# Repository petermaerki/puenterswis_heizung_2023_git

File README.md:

# puenterswis_heizung_2023
Puenterswis Heizungsersatz mit jeweils zwei Pellematic Maxi in Kaskade, PESK41, mit Brennwert, Touch V.4.04.
Steuerung der Ladung der dezentralen Wärmespeicher und des zentralen Pufferspeichers.

- [Erfahrungsbericht](./erfahrung_doku/readme.md)

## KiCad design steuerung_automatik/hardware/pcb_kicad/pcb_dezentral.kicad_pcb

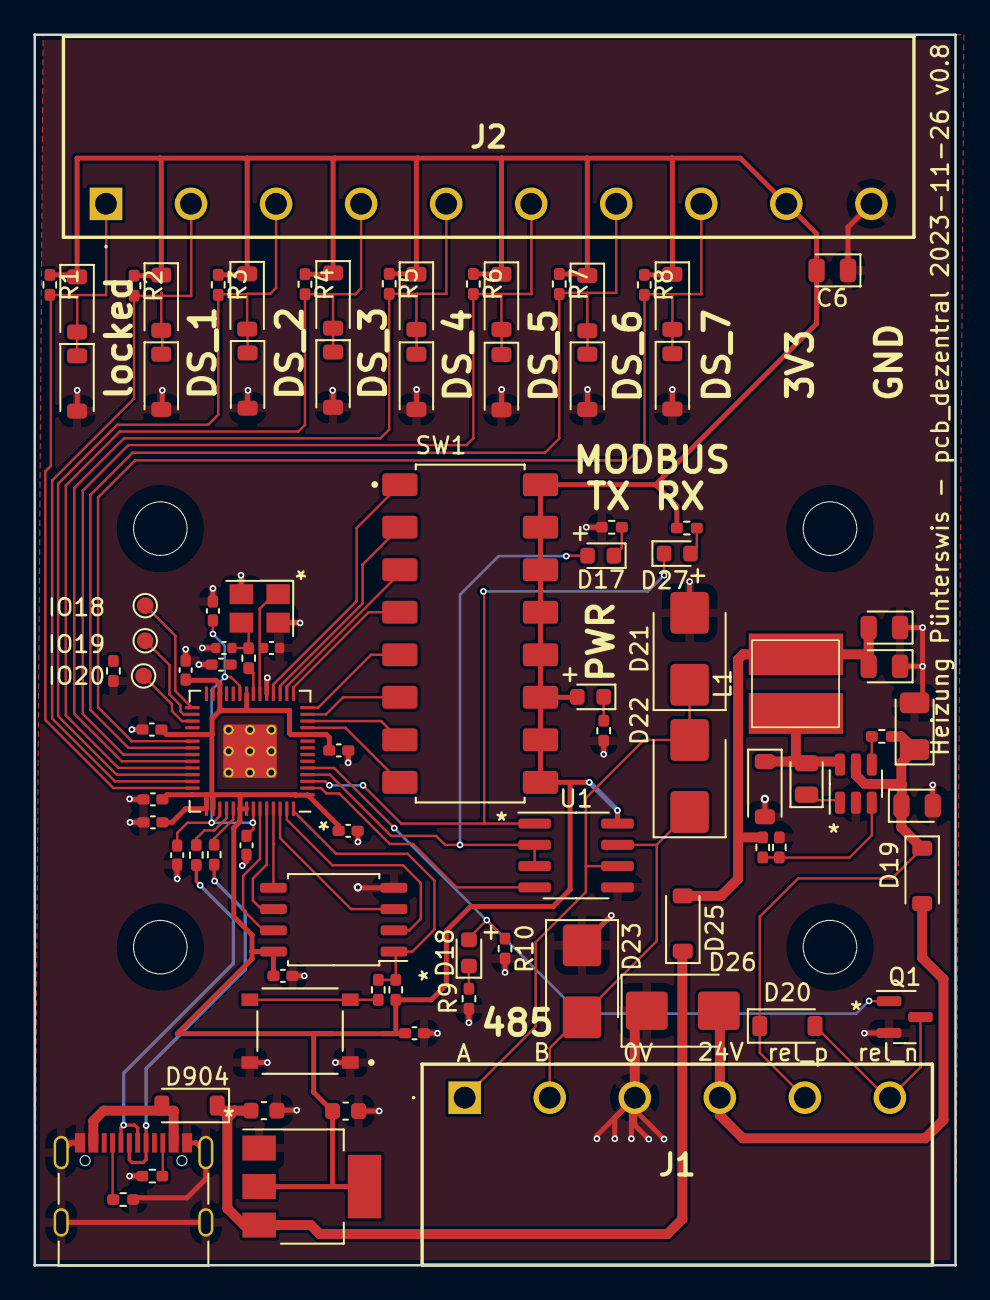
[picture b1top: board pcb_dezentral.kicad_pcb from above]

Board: 2 copper layers, 55.0 x 73.5 mm, 92 parts (0 on the bottom side), 58 nets.

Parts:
C1: 4u7 50V; D_1206_3216Metric
C2, C3, C5, C6: 100n 50V; D_0805_2012Metric
C4: 10u 25V; D_0805_2012Metric
C901, C902: 10u; C_0603_1608Metric
C903, C904, C907, C908, C911, C912, C913, C914, C915, C916: 100n; C_0402_1005Metric_Pad0.74x0.62mm_HandSolder
C905, C906: 1u; C_0402_1005Metric_Pad0.74x0.62mm_HandSolder
C909, C910: 30p; C_0402_1005Metric
D1, D2, D3, D4, D5, D6, D7, D8, D9, D10, D11, D12, D13, D14, D15, D16, D19, D20, D24, D25, D904: B5819W SL; D_SOD-123
D17: LED RED; LED_0603_1608Metric
D18: LED WHITE; LED_0603_1608Metric
D21, D22, D23: SMBJ6.5CA; D_SMB
D26: SMBJ30CA; D_SMB
D27: LED BLUE; LED_0603_1608Metric
D901: LED GREEN; LED_0603_1608Metric
HOLDER1: din_rail_pcb_holder
IO18, IO19, IO20: TestPoint; TestPoint_Pad_D1.0mm
J1: weidmueller_SL5.08HC-06-90
J2: weidmueller_SL5.08HC-10-90
J901: USB_C_Receptacle_USB2.0; USB_C_Receptacle_Palconn_UTC16-G
L1: 22uH; L_MODBUS
Q1: AO3400A; SOT-23
R1, R2, R3, R4, R5, R6, R7, R8, R14: 4k7; R_0402_1005Metric_Pad0.72x0.64mm_HandSolder
R9: 470; R_0402_1005Metric_Pad0.72x0.64mm_HandSolder
R10, R13: 10k; R_0402_1005Metric_Pad0.72x0.64mm_HandSolder
R11: 100k; R_0402_1005Metric_Pad0.72x0.64mm_HandSolder
R12: 56k; R_0402_1005Metric_Pad0.72x0.64mm_HandSolder
R15, R16, R905: 470R; R_0402_1005Metric_Pad0.72x0.64mm_HandSolder
R901, R902: 5.1K; R_0402_1005Metric_Pad0.72x0.64mm_HandSolder
R903, R904: 27R; R_0402_1005Metric_Pad0.72x0.64mm_HandSolder
R906: 1K; R_0402_1005Metric_Pad0.72x0.64mm_HandSolder
R907: 10K; R_0402_1005Metric_Pad0.72x0.64mm_HandSolder
R908: 1k; R_0402_1005Metric_Pad0.72x0.64mm_HandSolder
SW1: dip_switch_SPST16
SW901: SW_MEC_5E; SW_TS-1187A-B-A-B
U1: SP3485EN-L/TR; SOIC-8_3.9x4.9mm_P1.27mm
U2: AOZ1282CI; SOT-23-6
U901: RP2040; RP2040-QFN-56
U902: AMS1117-3.3; SOT-223-3_TabPin2
U903: W25Q128JVS; SOIC-8_5.23x5.23mm_P1.27mm
Y901: Crystal_GND24_Small; Crystal_SMD_3225-4Pin_3.2x2.5mm

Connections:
24Vp: C1.1, C2.1, D19.1 (K), D20.1 (K), J1.5, R11.1, U2.5 (VIN)
485_24V: D19.2 (A), D26.2 (A2), J1.4
485_A: D21.1 (A1), D22.2 (A2), J1.1, U1.6 (A)
485_B: D22.1 (A1), D23.2 (A2), J1.2, U1.7 (B)
+1V1: C903.1, C904.1, C905.1, U901.23 (DVDD), U901.45 (VREG-VOUT), U901.50 (DVDD)
+3V3: C6.2, C902.1, C906.1, C907.1, C908.1, C911.1, C912.1, C913.1, C914.1, C915.1, C916.1, D1.1 (K), D3.1 (K), D5.1 (K), D7.1 (K), D9.1 (K), D11.1 (K), D13.1 (K), D15.1 (K), D901.2 (A), J2.9, R1.1, R2.1, R3.1, R4.1, R5.1, R6.1, R7.1, R8.1, R15.1, R907.1, SW1.1-1, SW1.2-1, SW1.3-1, SW1.4-1, SW1.5-1, SW1.6-1, SW1.7-1, SW1.8-1, U1.8 (VCC), U901.1 (IOVDD), U901.10 (IOVDD), U901.22 (IOVDD), U901.26 (RUN), U901.33 (IOVDD), U901.42 (IOVDD), U901.43 (ADC-AVDD), U901.44 (VREG-VIN), U901.48 (USB-VDD), U901.49 (IOVDD), U902.2 (VO), U903.8 (VCC)
+5V: C901.1, D25.1 (K), D904.1 (K), U902.3 (VI)
/cpu/QSPI_SCLK: U901.52 (QSPI-SCLK), U903.6 (CLK)
/cpu/QSPI_SD0: U901.53 (QSPI-SD0), U903.5 (DI(IO0))
/cpu/QSPI_SD1: U901.55 (QSPI-SD1), U903.2 (DO(IO1))
/cpu/QSPI_SD2: U901.54 (QSPI-SD2), U903.3 (IO2)
/cpu/QSPI_SD3: U901.51 (QSPI-SD3), U903.7 (IO3)
/cpu/QSPI_SS: R906.2, R907.2, U901.56 (QSPI-SS-N), U903.1 (~CS)
/cpu/USB_D+: J901.A6 (D+), J901.B6 (D+), R903.1
/cpu/USB_D-: J901.A7 (D-), J901.B7 (D-), R904.1
/cpu/XIN: C909.1, U901.20 (XIN), Y901.1
/cpu/XOUT: R908.1, U901.21 (XOUT)
GND: C1.2, C2.2, C4.1, C5.1, C6.1, C901.2, C902.2, C903.2, C904.2, C905.2, C906.2, C907.2, C908.2, C909.2, C910.2, C911.2, C912.2, C913.2, C914.2, C915.2, C916.2, D2.2 (A), D4.2 (A), D6.2 (A), D8.2 (A), D10.2 (A), D12.2 (A), D14.2 (A), D16.2 (A), D21.2 (A2), D23.1 (A1), D24.2 (A), D26.1 (A1), J1.3, J2.10, J901.A1 (GND), J901.A12 (GND), J901.B1 (GND), J901.B12 (GND), J901.S1 (SHIELD), Q1.2 (S), R9.2, R10.2, R13.2, R14.2, R16.2, R901.2, R902.2, R905.1, SW901.1, SW901.2, U1.5 (GND), U2.2 (GND), U901.19 (TESTEN), U901.57 (GND), U902.1 (GND), U903.4 (GND), Y901.2, Y901.4
MODBUS_DE: D17.2 (A), R14.1, U1.2 (~RE), U1.3 (DE), U901.4 (GPIO2)
MODBUS_DI: U1.4 (DI), U901.2 (GPIO0)
MODBUS_RO: D27.1 (K), U1.1 (RO), U901.3 (GPIO1)
unnamed: C910.1, R908.2, Y901.3
unnamed: D17.1 (K), R16.1
unnamed: D18.1 (K), R9.1
unnamed: C3.2, D24.1 (K), L1.1, U2.6 (LX)
unnamed: C4.2, C5.2, D25.2 (A), L1.2, R12.2
unnamed: D27.2 (A), R15.2
unnamed: D901.1 (K), R905.2
unnamed: D904.2 (A), J901.A4 (VBUS), J901.A9 (VBUS), J901.B4 (VBUS), J901.B9 (VBUS)
unnamed: J901.A5 (CC1), R901.1
unnamed: J901.B5 (CC2), R902.1
unnamed: R906.1, SW901.3 (K), SW901.4 (A)
unnamed: C3.1, U2.1 (BST)
unnamed: R11.2, U2.4 (EN)
unnamed: R12.1, R13.1, U2.3 (FB)
unnamed: IO18.1, U901.29 (GPIO18)
unnamed: IO19.1, U901.30 (GPIO19)
unnamed: IO20.1, U901.31 (GPIO20)
unnamed: R904.2, U901.46 (USB-DM)
unnamed: R903.2, U901.47 (USB-DP)
ds_0: D1.2 (A), D2.1 (K), J2.1, R1.2, U901.41 (GPIO29/ADC3)
ds_1: D3.2 (A), D4.1 (K), J2.2, R2.2, U901.40 (GPIO28/ADC2)
ds_2: D5.2 (A), D6.1 (K), J2.3, R3.2, U901.39 (GPIO27/ADC1)
ds_3: D7.2 (A), D8.1 (K), J2.4, R4.2, U901.38 (GPIO26/ADC0)
ds_4: D9.2 (A), D10.1 (K), J2.5, R5.2, U901.37 (GPIO25)
ds_5: D11.2 (A), D12.1 (K), J2.6, R6.2, U901.36 (GPIO24)
ds_6: D13.2 (A), D14.1 (K), J2.7, R7.2, U901.35 (GPIO23)
ds_7: D15.2 (A), D16.1 (K), J2.8, R8.2, U901.34 (GPIO22)
modbus_addr_0: SW1.1, U901.18 (GPIO15)
modbus_addr_1: SW1.2, U901.17 (GPIO14)
modbus_addr_2: SW1.3, U901.16 (GPIO13)
modbus_addr_3: SW1.4, U901.15 (GPIO12)
modbus_addr_4: SW1.5, U901.14 (GPIO11)
modbus_addr_5: SW1.6, U901.13 (GPIO10)
modbus_addr_6: SW1.7, U901.12 (GPIO9)
modbus_addr_7: SW1.8, U901.11 (GPIO8)
rel: D18.2 (A), Q1.1 (G), R10.1, U901.5 (GPIO3)
rel_n: D20.2 (A), J1.6, Q1.3 (D)

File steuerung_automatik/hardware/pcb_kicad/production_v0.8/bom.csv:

Designator,Footprint,Quantity,Value,LCSC Part #
C1,1206,1,4u7 50V,C515689
"C2, C3, C5, C6",0805,4,100n 50V,C49678
C4,0805,1,10u 25V,C15850
"C901, C902",0603,2,10u,
"C903, C904, C907, C908, C911, C912, C913, C914, C915, C916",0402,10,100n,
"C905, C906",0402,2,1u,
"C909, C910",0402,2,30p,C1570
"D1, D10, D11, D12, D13, D14, D15, D16, D19, D2, D20, D24, D25, D3, D4, D5, D6, D7, D8, D9, D904",D_SOD-123,21,B5819W SL,C8598
D17,0603,1,LED RED,C2286
D18,0603,1,LED WHITE,C2290
"D21, D22, D23",D_SMB,3,SMBJ6.5CA,C7420377
D26,D_SMB,1,SMBJ30CA,C353367
D27,0603,1,LED BLUE,C189307
D901,0603,1,LED GREEN,C2297
J901,USB_C_Receptacle_Palconn_UTC16-G,1,USB_C_Receptacle_USB2.0,C165948
L1,L_MODBUS,1,22uH,C5289423
Q1,SOT-23,1,AO3400A,C20917
"R1, R14, R2, R3, R4, R5, R6, R7, R8",0402,9,4k7,
"R10, R13, R907",0402,3,10k,
R11,0402,1,100k,
R12,0402,1,56k,
"R15, R16, R905",0402,3,470R,
R9,0402,1,470,
"R901, R902",0402,2,5.1K,
"R903, R904",0402,2,27R,
"R906, R908",0402,2,1K,
SW1,dip_switch_SPST16,1,dip_switch_SPST16,C470473
SW901,SW_TS-1187A-B-A-B,1,SW_MEC_5E,C318884
U1,SOIC-8_3.9x4.9mm_P1.27mm,1,SP3485EN-L/TR,C8963
U2,SOT-23-6,1,AOZ1282CI,C111916
U901,RP2040-QFN-56,1,RP2040,C2040
U902,SOT-223-3_TabPin2,1,AMS1117-3.3,C6186
U903,SOIC-8_5.23x5.23mm_P1.27mm,1,W25Q128JVS,C97521
Y901,Crystal_SMD_3225-4Pin_3.2x2.5mm,1,Crystal_GND24_Small,C9002

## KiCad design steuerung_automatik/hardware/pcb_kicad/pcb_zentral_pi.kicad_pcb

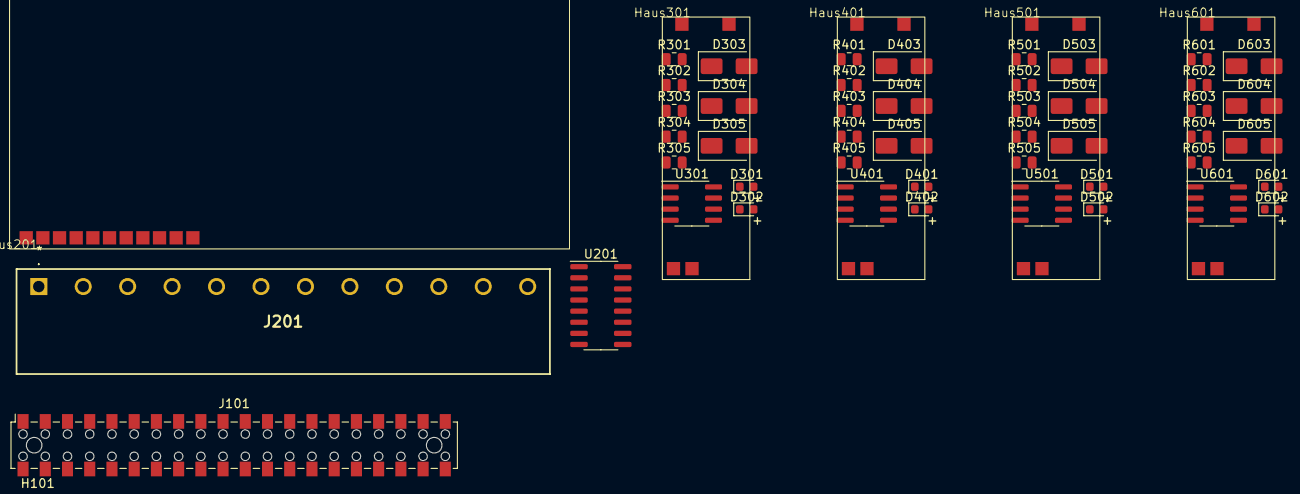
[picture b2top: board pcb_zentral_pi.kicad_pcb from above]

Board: 2 copper layers, 56 parts (0 on the bottom side), 34 nets, no tracks yet.

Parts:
D301, D401, D501, D601: LED GREEN; LED_0603_1608Metric
D302, D402, D502, D602: LED WHITE; LED_0603_1608Metric
D303, D304, D305, D403, D404, D405, D503, D504, D505, D603, D604, D605: SMAJ6.5CA; D_SMA
H101, H102, H103, H104: MountingHole; MountingHole_3.2mm_M3
Haus201: floor_Hausreihe
Haus301, Haus401, Haus501, Haus601: floor_Haus
J101: pi_zero; rpi_zero_bottom
J201: weidmueller_SL5.08HC-12-90
R301, R302, R401, R402, R501, R502, R601, R602: 470; R_0805_2012Metric
R303, R305, R403, R405, R503, R505, R603, R605: 4K7; R_0805_2012Metric
R304, R404, R504, R604: 120; R_0805_2012Metric
U201: shiftregister_74HC595; SOP-16_3.9x9.9mm_P1.27mm
U301, U401, U501, U601: SP3485EN-L/TR; SOIC-8_3.9x4.9mm_P1.27mm

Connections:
485_24V: Haus201.3 (485_24V), J201.2
+3V3: D301.2 (A), D401.2 (A), D501.2 (A), D601.2 (A), Haus201.1 (3V3), Haus301.3 (3V3), Haus401.3 (3V3), Haus501.3 (3V3), Haus601.3 (3V3), R305.2, R405.2, R505.2, R605.2, U301.8 (VCC), U401.8 (VCC), U501.8 (VCC), U601.8 (VCC)
/Hausreihe D/485_0V: Haus201.2 (485_0V), J201.1
/Hausreihe D/BIT_IN: Haus201.10 (BIT_IN), J101.12 (GPIO18), U201.14 (SER)
/Hausreihe D/BIT_OUT: Haus201.11 (BIT_OUT), U201.9 (QH')
/Hausreihe D/Haus R/A: D303.1 (A1), D304.2 (A2), Haus301.1 (A), J201.5, R303.2, R304.1, U301.6 (A)
/Hausreihe D/Haus R/B: D304.1 (A1), D305.2 (A2), Haus301.2 (B), J201.6, R304.2, R305.1, U301.7 (B)
/Hausreihe D/Haus R/MODBUS_DE: D302.2 (A), Haus301.8 (MODBUS_DE), U201.1 (QB), U301.3 (DE)
/Hausreihe D/Haus R/MODBUS_RE: Haus301.7 (MODBUS_RE), R301.2, U201.15 (QA), U301.2 (~RE)
/Hausreihe D/Haus S/A: D403.1 (A1), D404.2 (A2), Haus401.1 (A), J201.7, R403.2, R404.1, U401.6 (A)
/Hausreihe D/Haus S/B: D404.1 (A1), D405.2 (A2), Haus401.2 (B), R404.2, R405.1, U401.7 (B)
/Hausreihe D/Haus S/MODBUS_DE: D402.2 (A), Haus401.8 (MODBUS_DE), U401.3 (DE)
/Hausreihe D/Haus S/MODBUS_RE: Haus401.7 (MODBUS_RE), R401.2, U401.2 (~RE)
/Hausreihe D/Haus T/A: D503.1 (A1), D504.2 (A2), Haus501.1 (A), R503.2, R504.1, U501.6 (A)
/Hausreihe D/Haus T/B: D504.1 (A1), D505.2 (A2), Haus501.2 (B), R504.2, R505.1, U501.7 (B)
/Hausreihe D/Haus T/MODBUS_DE: D502.2 (A), Haus501.8 (MODBUS_DE), U501.3 (DE)
/Hausreihe D/Haus T/MODBUS_RE: Haus501.7 (MODBUS_RE), R501.2, U501.2 (~RE)
/Hausreihe D/Haus U/A: D603.1 (A1), D604.2 (A2), Haus601.1 (A), R603.2, R604.1, U601.6 (A)
/Hausreihe D/Haus U/B: D604.1 (A1), D605.2 (A2), Haus601.2 (B), R604.2, R605.1, U601.7 (B)
/Hausreihe D/Haus U/MODBUS_DE: D602.2 (A), Haus601.8 (MODBUS_DE), U601.3 (DE)
/Hausreihe D/Haus U/MODBUS_RE: Haus601.7 (MODBUS_RE), R601.2, U601.2 (~RE)
GND: D303.2 (A2), D305.1 (A1), D403.2 (A2), D405.1 (A1), D503.2 (A2), D505.1 (A1), D603.2 (A2), D605.1 (A1), R302.2, R303.1, R402.2, R403.1, R502.2, R503.1, R602.2, R603.1, U201.8 (GND), U301.5 (GND), U401.5 (GND), U501.5 (GND), U601.5 (GND)
MODBUS_DI: Haus201.4 (MODBUS_DI), Haus301.6 (MODBUS_DI), Haus401.6 (MODBUS_DI), Haus501.6 (MODBUS_DI), Haus601.6 (MODBUS_DI), J101.10 (GPIO15_RXD0), U301.4 (DI), U401.4 (DI), U501.4 (DI), U601.4 (DI)
MODBUS_RO: Haus201.5 (MODBUS_RO), Haus301.5 (MODBUS_RO), Haus401.5 (MODBUS_RO), Haus501.5 (MODBUS_RO), Haus601.5 (MODBUS_RO), J101.8 (GPIO14_TXD0), U301.1 (RO), U401.1 (RO), U501.1 (RO), U601.1 (RO)
unnamed: D301.1 (K), R301.1
unnamed: D302.1 (K), R302.1
unnamed: D401.1 (K), R401.1
unnamed: D402.1 (K), R402.1
unnamed: D501.1 (K), R501.1
unnamed: D502.1 (K), R502.1
unnamed: D601.1 (K), R601.1
unnamed: D602.1 (K), R602.1
SHIFTREGISTER_CLOCK: Haus201.6 (SHIFTREGISTER_CLOCK), J101.18 (GPIO24), U201.11 (SRCLK)
SHIFTREGISTER_OE: Haus201.7 (SHIFTREGISTER_OE), J101.16 (GPIO23), U201.13 (~OE)

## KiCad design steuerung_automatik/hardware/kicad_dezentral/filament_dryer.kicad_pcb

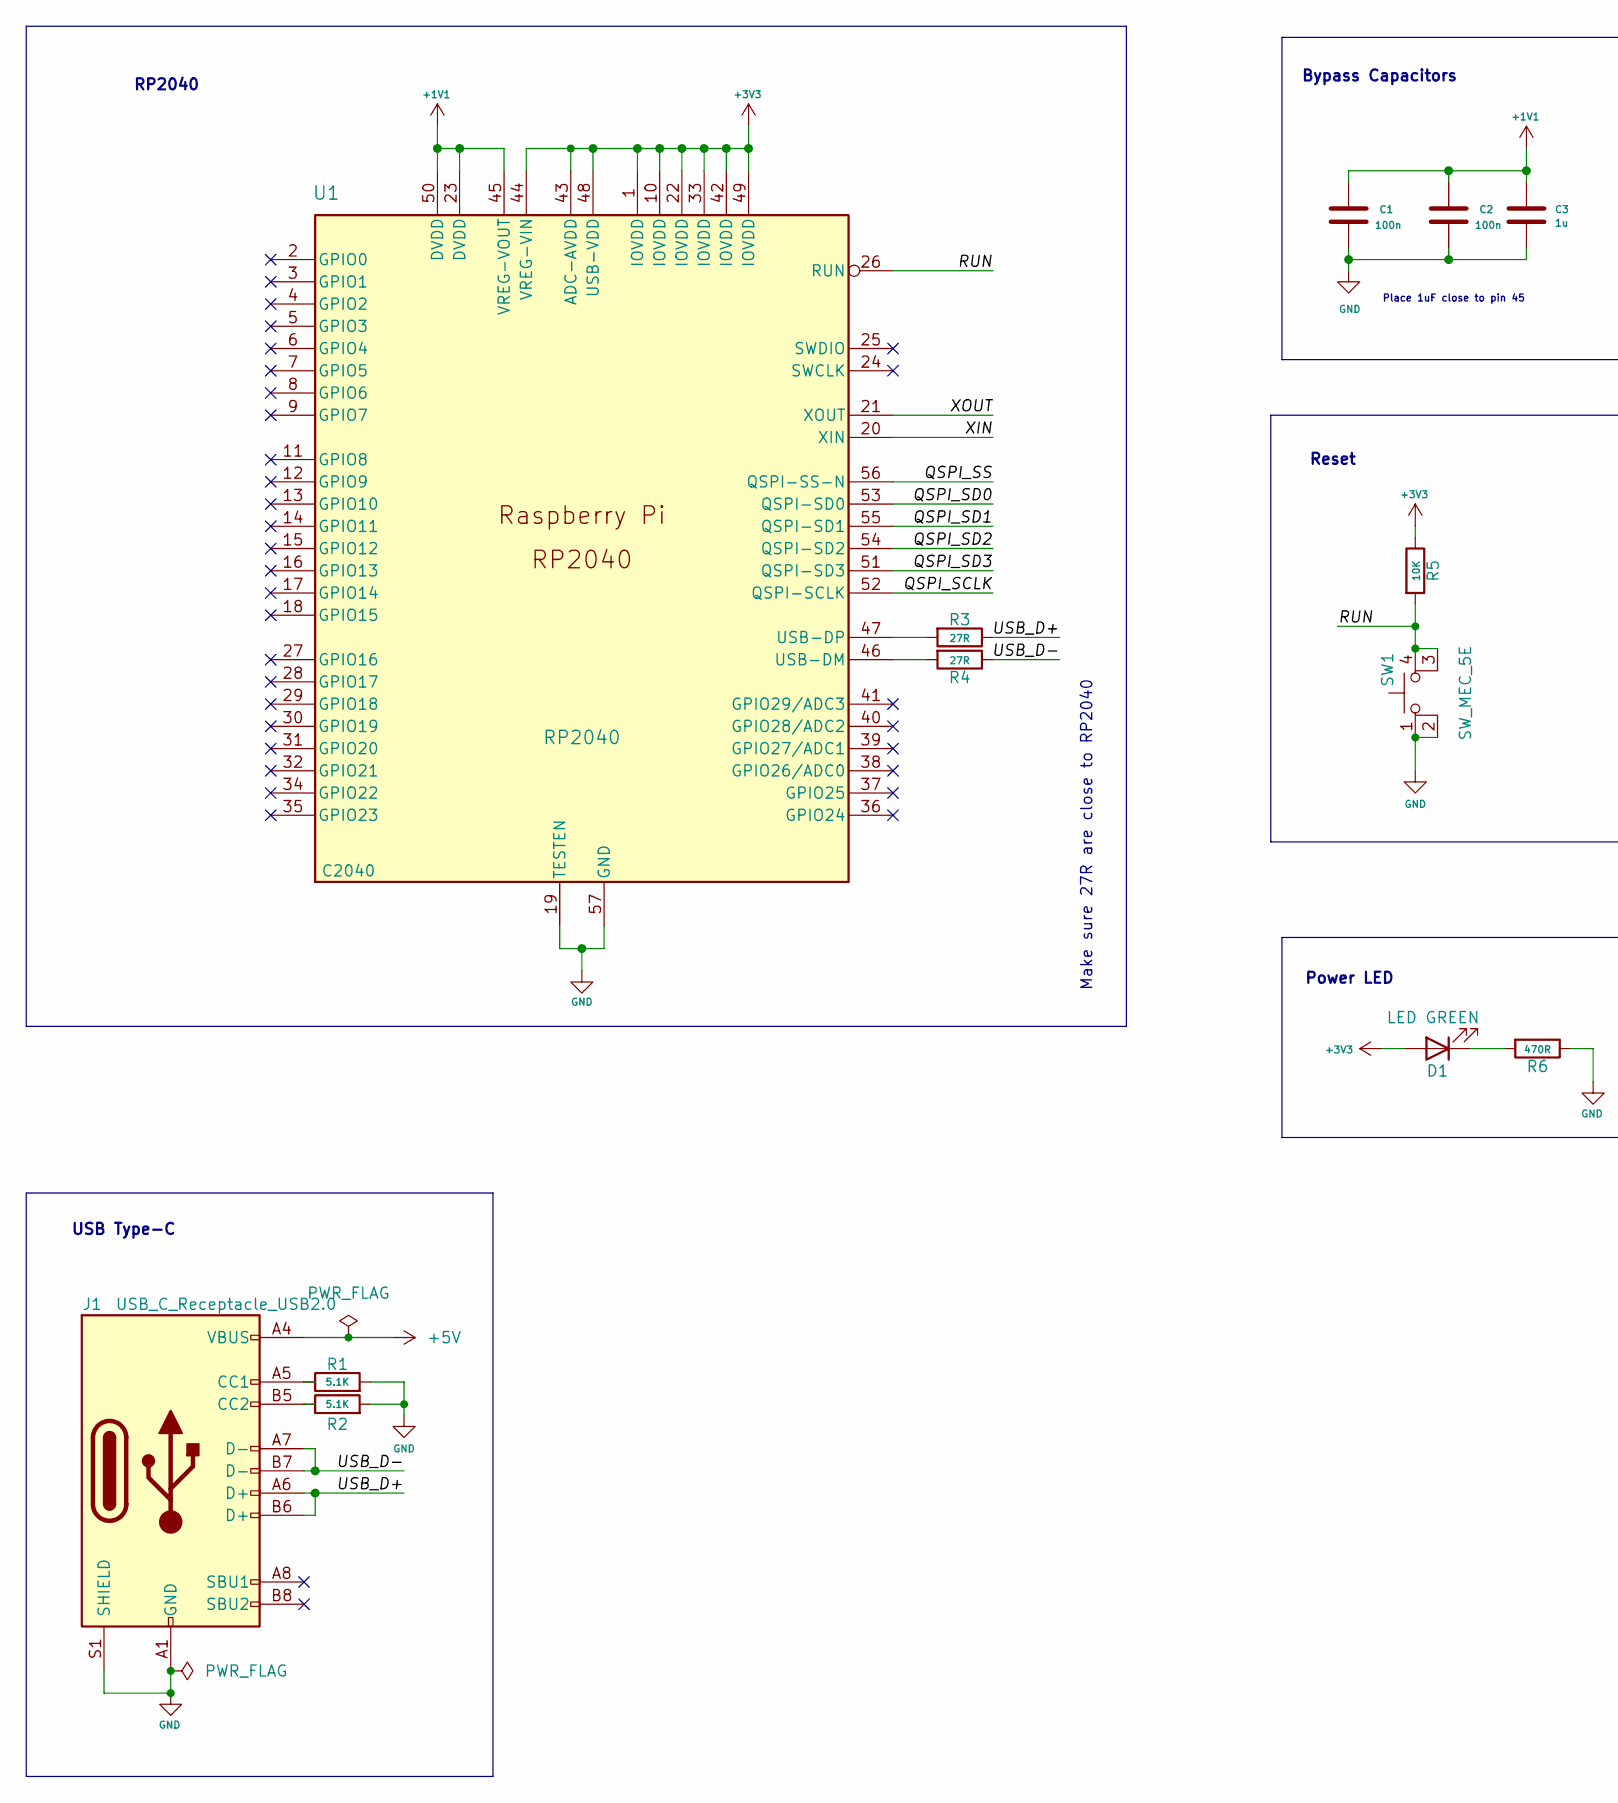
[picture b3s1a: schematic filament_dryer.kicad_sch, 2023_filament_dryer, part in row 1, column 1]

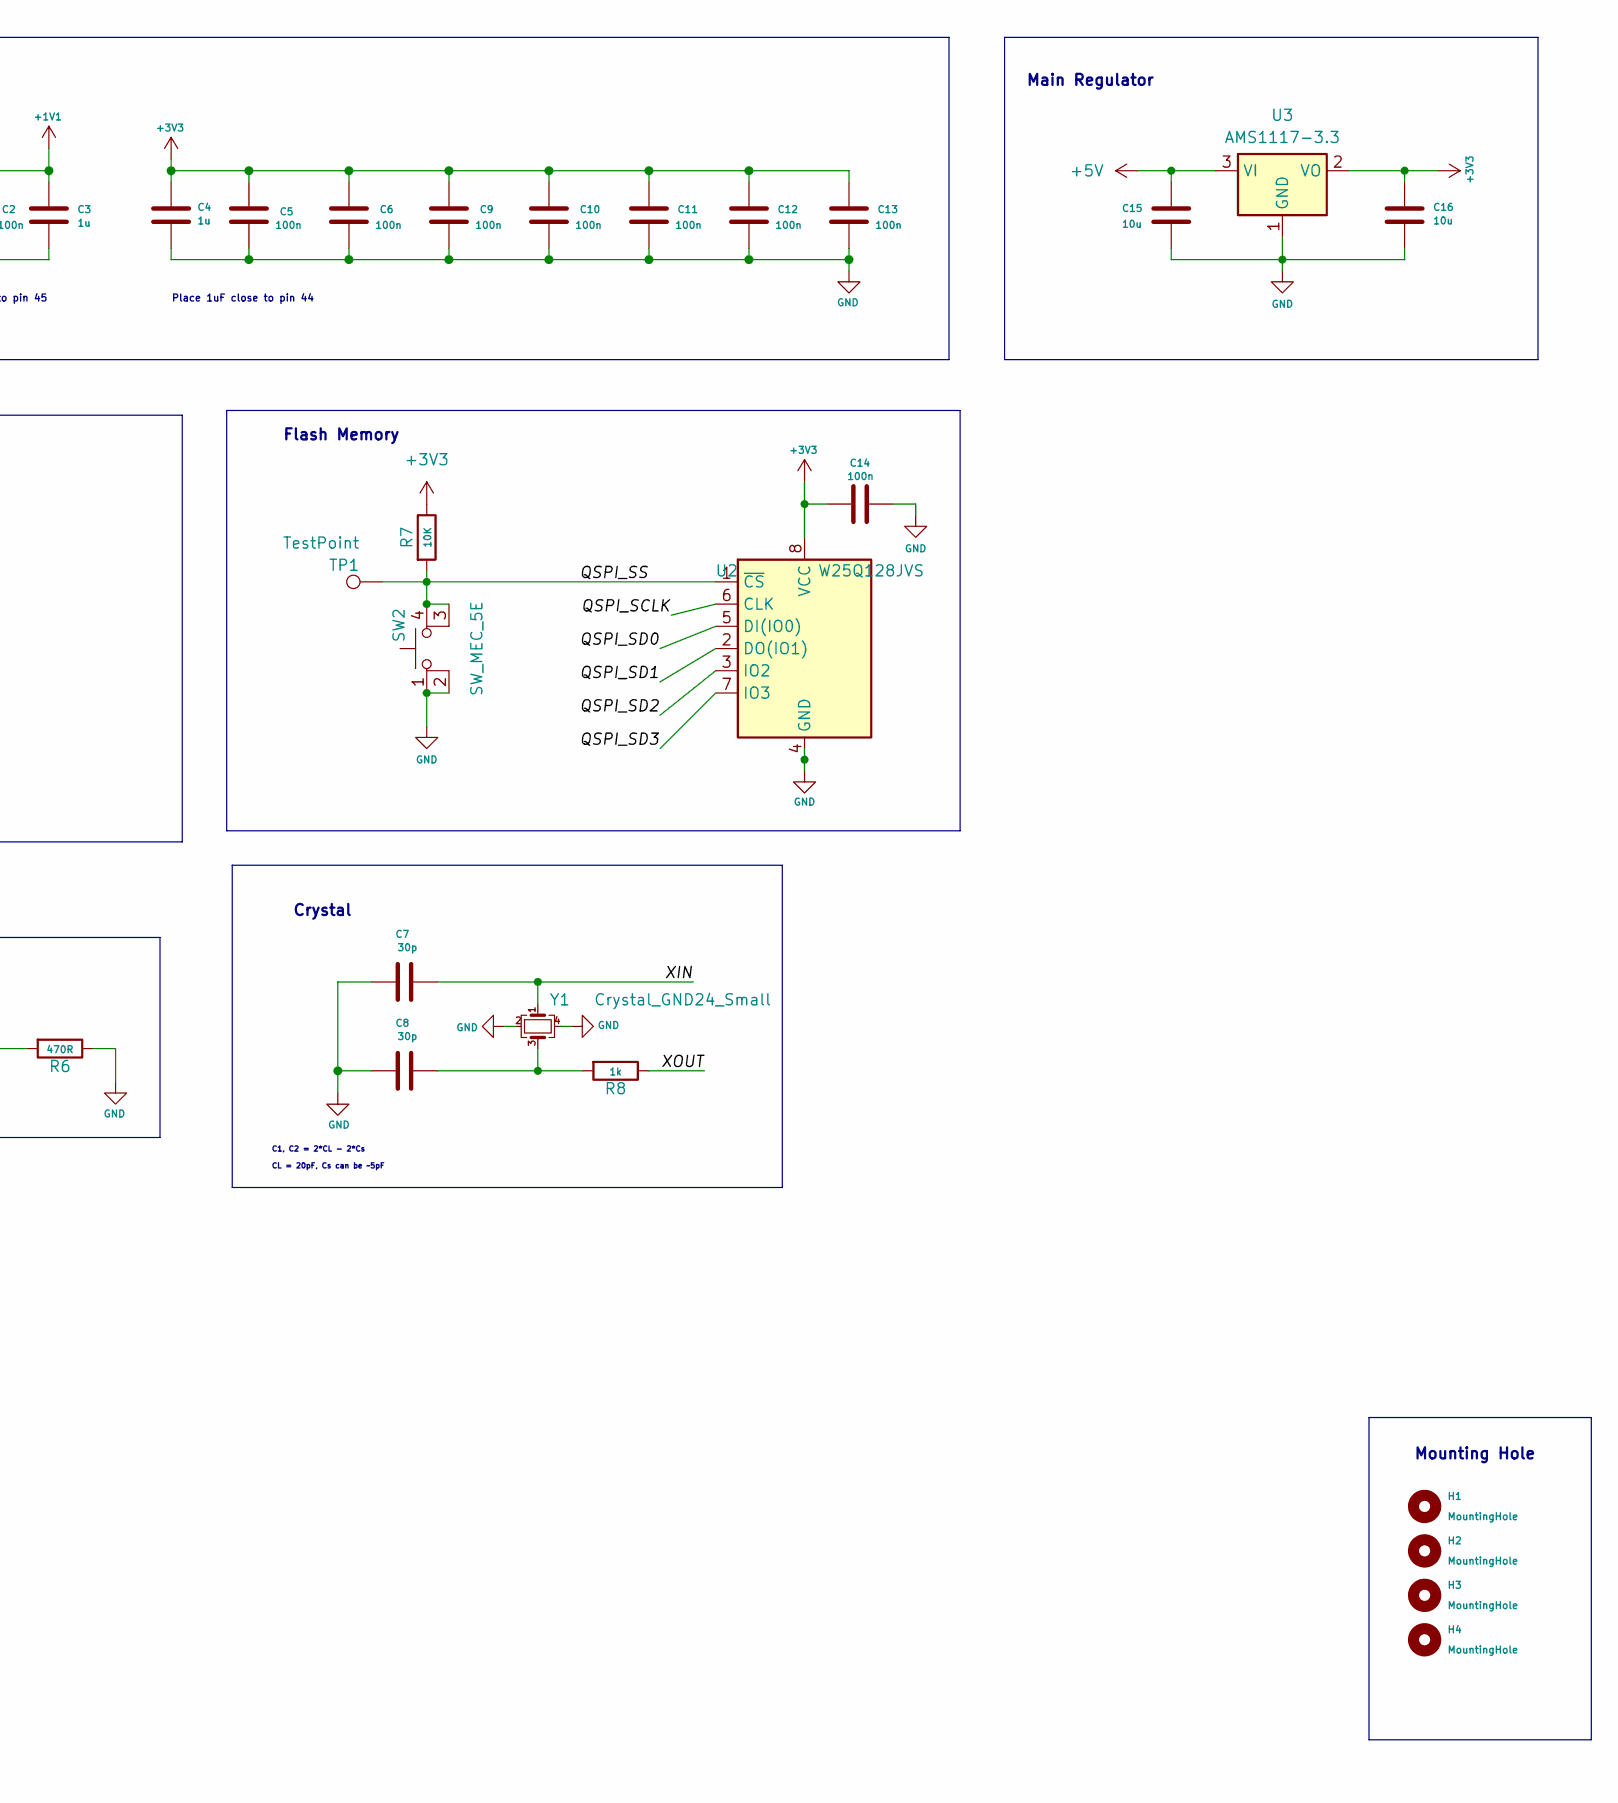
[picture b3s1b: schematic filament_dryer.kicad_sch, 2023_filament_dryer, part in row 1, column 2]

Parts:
C1, C2, C5, C6, C9, C10, C11, C12, C13, C14: 100n; C_0402_1005Metric_Pad0.74x0.62mm_HandSolder
C3, C4: 1u; C_0402_1005Metric_Pad0.74x0.62mm_HandSolder
C7, C8: 30p; C_0402_1005Metric; JLC C1570
C15, C16: 10u; C_0603_1608Metric
D1: LED GREEN; LED_0603_1608Metric; JLC C2297
H1, H2, H3, H4: MountingHole; MountingHole_3.2mm_M3
J1: USB_C_Receptacle_USB2.0; USB_C_Receptacle_Palconn_UTC16-G; JLC C165948
R1, R2: 5.1K; R_0402_1005Metric_Pad0.72x0.64mm_HandSolder
R3, R4: 27R; R_0402_1005Metric_Pad0.72x0.64mm_HandSolder
R5, R7: 10K; R_0402_1005Metric_Pad0.72x0.64mm_HandSolder
R6: 470R; R_0402_1005Metric_Pad0.72x0.64mm_HandSolder
R8: 1k; R_0402_1005Metric_Pad0.72x0.64mm_HandSolder
SW1, SW2: SW_MEC_5E; SW_TS-1187A-B-A-B; JLC C318884
TP1: TestPoint; TestPoint_Pad_D2.5mm
U1: RP2040; QFN-56-1EP_7x7mm_P0.4mm_EP5.6x5.6mm; JLC C2040
U2: W25Q128JVS; SOIC-8_5.23x5.23mm_P1.27mm; JLC C97521
U3: AMS1117-3.3; SOT-223-3_TabPin2; JLC C6186
Y1: Crystal_GND24_Small; Crystal_SMD_3225-4Pin_3.2x2.5mm; JLC C9002

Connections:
+1V1: C1.1, C2.1, C3.1, U1.23 (DVDD), U1.45 (VREG-VOUT), U1.50 (DVDD)
+3V3: C4.1, C5.1, C6.1, C9.1, C10.1, C11.1, C12.1, C13.1, C14.1, C16.1, D1.2 (A), R5.1, R7.1, U1.1 (IOVDD), U1.10 (IOVDD), U1.22 (IOVDD), U1.33 (IOVDD), U1.42 (IOVDD), U1.43 (ADC-AVDD), U1.44 (VREG-VIN), U1.48 (USB-VDD), U1.49 (IOVDD), U2.8 (VCC), U3.2 (VO)
+5V: C15.1, J1.A4 (VBUS), J1.A9 (VBUS), J1.B4 (VBUS), J1.B9 (VBUS), U3.3 (VI)
/QSPI_SCLK: U1.52 (QSPI-SCLK), U2.6 (CLK)
/QSPI_SD0: U1.53 (QSPI-SD0), U2.5 (DI(IO0))
/QSPI_SD1: U1.55 (QSPI-SD1), U2.2 (DO(IO1))
/QSPI_SD2: U1.54 (QSPI-SD2), U2.3 (IO2)
/QSPI_SD3: U1.51 (QSPI-SD3), U2.7 (IO3)
/QSPI_SS: R7.2, SW2.3 (K), SW2.4 (A), TP1.1, U1.56 (QSPI-SS-N), U2.1 (~CS)
/RUN: R5.2, SW1.3 (K), SW1.4 (A), U1.26 (RUN)
/USB_D+: J1.A6 (D+), J1.B6 (D+), R3.1
/USB_D-: J1.A7 (D-), J1.B7 (D-), R4.1
/XIN: C7.1, U1.20 (XIN), Y1.1
/XOUT: R8.1, U1.21 (XOUT)
GND: C1.2, C2.2, C3.2, C4.2, C5.2, C6.2, C7.2, C8.2, C9.2, C10.2, C11.2, C12.2, C13.2, C14.2, C15.2, C16.2, J1.A1 (GND), J1.A12 (GND), J1.B1 (GND), J1.B12 (GND), J1.S1 (SHIELD), R1.2, R2.2, R6.1, SW1.1, SW1.2, SW2.1, SW2.2, U1.19 (TESTEN), U1.57 (GND), U2.4 (GND), U3.1 (GND), Y1.2, Y1.4
unnamed: C8.1, R8.2, Y1.3
unnamed: D1.1 (K), R6.2
unnamed: J1.A5 (CC1), R1.1
unnamed: J1.B5 (CC2), R2.1
unnamed: R4.2, U1.46 (USB-DM)
unnamed: R3.2, U1.47 (USB-DP)

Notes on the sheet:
Mounting Hole
USB Type-C
Main Regulator
RP2040
Bypass Capacitors
Place 1uF close to pin 45
Crystal
Power LED
Make sure 27R are close to RP2040
C1, C2 = 2*CL - 2*Cs CL = 20pF, Cs can be ~5pF
Reset
Place 1uF close to pin 44
Flash Memory

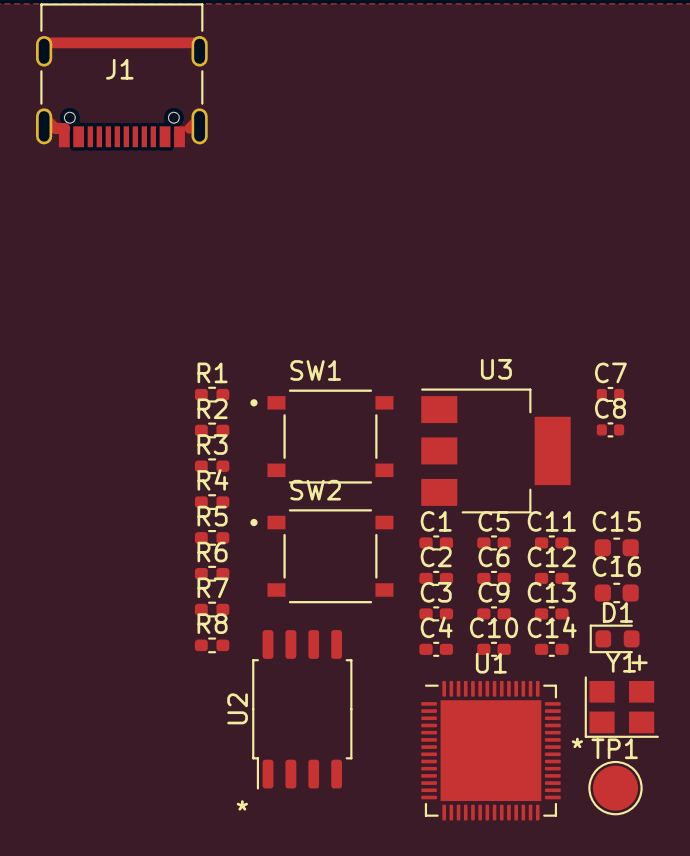
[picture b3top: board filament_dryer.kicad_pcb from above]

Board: 2 copper layers, 37 parts (0 on the bottom side), 21 nets.

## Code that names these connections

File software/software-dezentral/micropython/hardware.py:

import time
import machine

from umodbus.asynchronous.serial import AsyncModbusRTU

from util_constants import DEVELOPMENT
from util_DS18X20 import Ds

UART_MODBUS_ID = 0
GPIO_MODBUS_DI = 0
GPIO_MODBUS_RO = 1
GPIO_MODBUS_DE = 2

GPIO_MODBUS_ADDRS = (
    "GPIO8",
    "GPIO9",
    "GPIO10",
    "GPIO11",
    "GPIO12",
    "GPIO13",
    "GPIO14",
    "GPIO15",
)
PIN_MODBUS_ADDR = [machine.Pin(gpio, machine.Pin.PULL_DOWN) for gpio in GPIO_MODBUS_ADDRS]

GPIO_DS = (
    "GPIO29",
    "GPIO28",
    "GPIO27",
    "GPIO26",
    "GPIO25",
    "GPIO24",
    "GPIO23",
    "GPIO22",
)


class Hardware:
    LIMIT_UPTIME_MS = (1200 if DEVELOPMENT else 12 * 60 * 60) * 1000

    def __init__(self):
        self._ticks_boot_ms = time.ticks_ms()

        """
        If None, LIMIT_UPTIME_S has been reached.
        """
        self.PIN_RELAIS = machine.Pin(3, machine.Pin.OUT)
        self.PIN_RELAIS.on()
        self.PIN_DS_OK_LED = machine.Pin(20, machine.Pin.OUT)
        self.PIN_DS_OK_LED.off()
        self.PIN_BUTTON_ZENTRALE = machine.Pin(4, machine.Pin.IN)
        self.PIN_LED_ZENTRALE = machine.Pin(6, machine.Pin.OUT)
        self.PIN_DS_OK_LED.on()

        self.led_zentrale_blink = False
        self.led_zentrale_on = False

        def cb_led_zentrale_blink(t):
            if self.led_zentrale_blink:
                self.PIN_LED_ZENTRALE.toggle()

        machine.Timer(period=500, mode=machine.Timer.PERIODIC, callback=cb_led_zentrale_blink)

        # Make sure we release the modbus!
        machine.Pin(GPIO_MODBUS_DE, machine.Pin.OUT).off()
        self.modbus_server_addr = self.dip_switch_addr
        self.modbus = AsyncModbusRTU(
            addr=self.modbus_server_addr,
            uart_id=UART_MODBUS_ID,
            pins=(GPIO_MODBUS_DI, GPIO_MODBUS_RO),  # (TX, RX)
            ctrl_pin=GPIO_MODBUS_DE,
            baudrate=9600,
            data_bits=8,
            stop_bits=1,
            parity=None,
        )

        self.sensors_ds = [Ds(gpio) for gpio in GPIO_DS]

    def handle_ds_ok_led(self) -> None:
        """
        The 'DS OK' LED should be on when all temperature sensors
        in use work fine.
        """
        # The first two sensors are not in use
        DS_NOT_IN_USE = 2
        ds_ok = True
        for ds in self.sensors_ds[DS_NOT_IN_USE:]:
            # if not ds.history.last_ok:
            if not ds.ok:
                ds_ok = False
        self.PIN_DS_OK_LED.value(ds_ok)

    @property
    def dip_switch_changed(self) -> bool:
        new_addr = self.dip_switch_addr
        changed = new_addr != self.modbus_server_addr
        if changed:
            print(f"Dip Switch changed from {self.modbus_server_addr} to {new_addr}: reset()")
        return changed

    @property
    def uptime_ms(self) -> int:
        """
        'uptime_ms()' will start from 0 when the RP2 starts or soft-resets.
        The time will be limited to LIMIT_UPTIME_S.
        """
        if self._ticks_boot_ms is None:
            return self.LIMIT_UPTIME_MS

        # See: https://docs.micropython.org/en/latest/library/time.html#time.ticks_ms
        uptime_ms = time.ticks_diff(time.ticks_ms(), self._ticks_boot_ms)

        if uptime_ms < self.LIMIT_UPTIME_MS:
            return uptime_ms

        self._ticks_boot_ms = None
        return self.LIMIT_UPTIME_MS

    @property
    def dip_switch_addr(self) -> int:
        """
        Read the dipswitch and return the modbus address
        """
        addr = 0
        for pin in PIN_MODBUS_ADDR:
            addr *= 2
            if pin.value():
                addr += 1
        return addr

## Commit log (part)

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2023-12-22 Cloned from https://github.com/GimmickNG/pycopy-modbus/tree/mpmodbus-compatibility
2023-12-24 Bugfix: value from on_get_cb was swallowed
2023-12-24 Initial implementation dezentral
2023-12-25 Review mit Peter
2023-12-26 Review mit Peter 2
2023-12-27 Modbus debugging mit Peter
2023-12-28 Optimize modbus error rate
2023-12-28 New: fork-uModbus
2024-01-05 Wichtige Werte Modbus
2024-01-05 pcb_decentral: To be fixed
2024-01-05 example belimo
2024-01-05 tmp 5
2024-01-05 Branch improve-uart_read_frame
2024-01-05 New: controller_pymodbus
2024-01-05 tmp 2
2024-01-05 Modbus Gauge / controller
2024-01-05 tmp 4
2024-01-05 tmp 1
2024-01-05 mischventil tcp/ip funktioniert
2024-01-17 cleaned up
2024-01-21 Kabelbaum
2024-01-22 Doku PCB
2024-01-25 Pi4 und Analog zu Mischventil
2024-01-25 Kabelverteiler
2024-01-27 pymodbus asyncio
2024-01-28 Kabelfarben
2024-02-04 BOM: C515689 -> C2897622
2024-02-04 Feedback jlcpcb
2024-02-04 software-dezentral: pymodbus asyncio
2024-02-04 reorder folders
2024-02-10 Beschriftung Durchgangsklemmen
2024-02-11 Weitere Planung
2024-02-11 Kosmetik.
2024-02-11 Elfero
2024-02-11 New: PIN_DS_OK
2024-02-11 Implement influxdb/grafana
2024-02-11 Add scenarios and configure ruff
2024-02-13 3D Modelle
2024-02-14 Kabelkonfektion
2024-02-16 Improve delta_C
2024-02-17 Kosmetik
2024-02-17 Improve statemachine logging
2024-02-22 peter_inbetriebnahme_windows_python3.9
2024-02-25 Add dezentral micropython firmware
2024-03-02 Implemented: Hardwaretest
2024-03-09 SETGET16BIT_ALL_FAST
2024-03-09 RelaisGpioBits -> GpioBits
2024-03-09 PI bringup
2024-03-09 Disable error history dezentral
2024-03-10 Beschriftung
2024-03-10 Modbus Probleme.
2024-03-17 public key probook peter
2024-03-17 Modbus error handling
2024-03-17 ssh tunnel
2024-03-17 run_zentral
2024-03-18 timouterror
2024-03-26 jupyter tests
2024-03-26 Codierbruecken
2024-03-27 Neue Messposition dezentral mitte.
2024-03-29 Ladestand
2024-03-29 update zero base image
2024-03-29 zero: simplify ssh-tunnel services
2024-03-29 Automatically load etappe. bucket 'heizung'.
2024-03-29 etappe tag
2024-03-30 Gitignore angepasst, kosmetik.
2024-03-30 Neu: sp_ladung
2024-03-31 util_transition
2024-03-31 Fix import
2024-04-02 Schlaufkasten
2024-04-14 Improve modbus logging. grafana uptime_s.
2024-04-14 ScenarioHausPicoRebootReset
2024-04-20 Improved Modbus error handling
2024-04-29 Add timestamp to influxdb records
2024-05-01 Add repl
2024-05-04 dezentral v0.1.3 / Bugfix reading relais_valve_open / Bugfix changed()
2024-05-04 controller_simple
2024-05-05 relais_valve_open -> relais_valve_open2 (now float with offset)
2024-05-05 relais_valve_open2 -> relais_valve_open
2024-05-05 doku
2024-05-05 trigger scope on modbus errors
2024-05-15 Bugfix hardwaretest
2024-05-19 dezentral v0.1.4 / Relais now on after boot
2024-05-19 WHILE_HARGASSNER
2024-05-19 controller_mischventil
2024-05-19 Hardware test testen
2024-05-19 Ausbaustufe E1
2024-05-20 Zeiten Hardwaretest neu 40+40+40s
2024-05-21 controller mischventil
2024-05-21 mischventil optimiert
2024-05-22 Status drehschalterauto_regenl/manuell konsistent nach hardwaretest
2024-06-05 Schaltpunkte Elfero hoeher
2024-06-14 WHILE_HARGASSNER steuert neu 'relais_6_pumpe'
2024-06-17 Neu 'haus_maerki'
2024-06-22 Cleanup util_history_modbus
2024-06-22 Berechnung Verlustleistung dezentral
2024-06-23 Improved error handliing
2024-06-23 Bugfix Verbrauch Haus
2024-06-23 Fastapi now starts Vertrauch task too.
2024-07-06 Entlueftungsschluessel
2024-07-07 Zentrale weiter ausgearbeitet, Umbenennungen
2024-07-10 Neu: util_history_verbrauch.py
2024-07-10 Mischventil: stellwert_V / stellwert_100
2024-07-10 mv raspi_os_config.py to raspi_os_config_template.py
2024-07-10 relais_0_mischventil_automatik
2024-07-12 New: PcbsDezentralHeizzentrale
2024-07-18 util_persistence
2024-07-18 mocked version fixed. Converted tests to pytest.
2024-07-18 modbus stability issued: increase TIMEOUT_AFTER_MODBUS_NO_RESPONSE_S
2024-07-19 Doku nachgefuehrt
2024-07-30 New: ScenarioHausSpTemperatureDiscrepancy
2024-07-30 hsm_dezentral: Fehlerverhalten implementiert und getestet
2024-07-30 Log dezentral version numbers
2024-07-30 New: exception_handler_and_exit
2024-07-30 zentral: ASYNCIO_TASK_HSM_DEZENTRAL_S
2024-07-30 Schema.
2024-07-30 Manuelle Tests
2024-07-30 util_persistence tested on puent.
2024-07-30 Cleanup application startup
2024-07-30 Doku.
2024-07-30 Doku Brennzyklen
2024-07-30 Implement 'PersistenceLegionellen'
2024-07-30 Ordnerstruktur angepasst
2024-07-30 Ordner: steuerung_automatik -> software
2024-07-30 Now flushes file when system goes down
2024-07-30 Bugfix
2024-08-04 Datenblaetter.
2024-08-04 PCB_DEZENTRAL Temperatursensoren aktualisiert.
2024-08-04 Oekofen modbus vorbereitet
2024-08-04 Heizzentrale Ventilator
2024-08-06 Ventilator
2024-08-07 util_controller_verbrauch_schaltschwelle.py
2024-08-07 Namensgebung
2024-08-08 Legionellen kill
2024-08-08 Influx: next_legionellen_kill_d
2024-08-08 schaltschwelle: Neu find_anhebung()
2024-08-08 relais zentral auf grafan
2024-08-08 Improved app termination
2024-08-08 Add scipy to requirements.txt. scipy performance tests.
2024-08-09 pytest for: zentral/util_persistence_legionellen.py
2024-08-09 pytest for: zentral/util_persistence_legionellen.py 2
2024-08-13 Controller Haeuser
2024-08-17 Elektro Heizsstab
2024-08-22 Add ScenarioHausValveOpenCloseOthers
2024-08-25 Bugfix influx
2024-08-28 Elektroeinsatz
2024-09-05 Fix modbux register readings of Mischventil
2024-09-06 relais_1_elektro_notheizung
2024-09-06 hargassner entfernt
2024-09-06 New: ControllerMischventilNone
2024-09-06 ControllerHaeuser: Fix constructor
2024-09-06 Vor ControllerHaueserSimple test
2024-09-06 Nach ControllerHaueserSimple test
2024-09-06 controller_haeuser: Simplify parameter list
2024-09-06 ScenarioOverwriteRelais6PumpeGesperrt
2024-09-06 Fix pumpe ein / gesperrt
2024-09-06 Aussentemperatur
2024-09-08 Neu: temperatur_aussen_C
2024-09-08 LadungBodenheizung is_sommer
2024-09-08 util_sp_ladung.py -> util_sp_ladung_dezentral.py
2024-09-08 New: LadungZentral
2024-09-13 Neu: BETRIEB_ELEKTRO_NOTHEIZUNG
2024-09-13 First successful mbus experiments
2024-09-13 MBus: Read data from Wärmezähler and sends it to influx
2024-09-13 Tuning peter
2024-09-13 Inbetriebnahme Bochslen
2024-09-14 Taussen_C -> TaussenU_C
2024-09-14 Nicer logging. Improved modbus_relais
2024-09-14 Neu: Bochs/Puent Ventilatoren
2024-09-14 Inbetriebnahme Controller Mischventil
2024-09-14 messung delay controller mischventil
2024-09-15 Regler Notheizung neu
2024-09-15 Update scenarios
2024-09-18 pumpe_ein_falls_speicher_genug_warm
2024-09-19 Peter: Tuning Temperaturen
2024-09-19 New: PersistenceMischventil
2024-09-20 Neu: ControllerHaeuserValveOpenIterator
2024-09-20 Mbus-Nummer Haus 19
2024-09-22 Waermezaehler
2024-09-23 Cleanup Modbus Addresses
2024-09-24 First oekofen implementation
2024-09-26 Tsz4_C > 65.0
2024-09-27 procent -> percent
2024-09-27 Bugfix 'relais_1_elektro_notheizung=None'
2024-09-27 New: brenner_uebersicht_prozent
2024-09-28 Erster Versuch controller_oekofen
2024-09-29 New: controller_oekofen
2024-09-29 Neu: SpZentralLevel
2024-09-29 _PUMPE_OFF_DURATION_S, abschalten_zweiter_Brenner, set_modulation_min
2024-10-02 Refactor
2024-10-02 Rewrite 'zwei_brenner'
2024-10-02 Rework ladung_prozent()
2024-10-03 New: util_action.py
2024-10-04 Massive rework.
2024-10-04 Cleanup HandlerAnhebung()
2024-10-04 Fix: util_controller_verbrauch_schaltschwelle_test.py
2024-10-04 Cleanup todo/obsolete
2024-10-04 Fix: zentral/controller_mischventil_test.py
2024-10-04 Fix util_modulation_soll.py
2024-10-04 Remove: ControllerMasterABC
2024-10-04 pylint
2024-10-04 BrennerModulation berücksichtigt echte Daten: BrennerZustaende
2024-10-04 Bigfix Anhebung Peter
2024-10-04 Grafana: mbus_sum_power_W
2024-10-04 Reactivate ScenarioOekofenBrennerModulation
2024-10-04 Bugfix: pumpe_is_on
2024-10-04 Remove: BrennerAction.NICHTS
2024-10-05 controller_master optimieren
2024-10-05 Einschaltverhalten Relais
2024-10-05 Refactoring SpLadungZentral
2024-10-05 solltemperatur_Tfv_C abhaengig von legionellen_kill
2024-10-05 Fix: update_last_hvv
2024-10-05 Move code-workspace to software folder
2024-10-05 Neue Reglergrenzen
2024-10-09 Neu: Lasthandler
2024-10-09 Modbus Oekofen retries, Fehlerhandling Oekofen
2024-10-09 Enable hardware watchdog
2024-10-09 HEATING_FULL_POWER
2024-10-09 individuell_prozent
2024-10-10 Improved: handle_brenner_mit_stoerung
2024-10-10 Sperrzeit zweiter Brenner
2024-10-10 Modbus Oekofen: retries
2024-10-10 mypy, pylint and ruff
2024-10-11 0 Brenner: anzahl_brenner_on=0
2024-10-11 Emergency Preventer
2024-10-11 New: grafana-reihe
2024-10-11 Dashboard backup
2024-10-15 neue strategie valve open/close
2024-10-15 Remove: emergency_preventer_bonus
2024-10-15 AUTOMATISCH_BRENNT_NICHT: -20 -> 0
2024-10-15 manual_test_zentral_oekofen_lost.md
2024-10-15 Remove state_ok_drehschalterauto_manuell|regeln
2024-10-15 Bugfix ScenarioHausSpTemperatureIncrease
2024-10-15 Kaminfeger AUS schaltet Brenner aus
2024-10-16 Fix endless loop in increase_valve_open_count()
2024-10-16 Do not crash if haus not reachable by mbus
2024-10-16 Fixed: ScenarioHausSpTemperatureDiscrepancy
2024-10-16 New: OEKOFEN_MODBUS_CONTROL_ON
2024-10-16 Legionellen_kill update
2024-10-16 UW Freigabehysterese neu auf -15K, daher keine Abhaengigkeit von TPO
2024-10-18 temp 01
2024-10-18 temp 03
2024-10-18 temp 04
2024-10-18 Burnout
2024-10-19 Legionellen eher starten
2024-10-21 Mischventil Energy in influx
2024-10-21 Notbehelf Brenner error zurück setzen falls alt
2024-10-23 Grafana Brenner soll ausblenden bei Drehschalter Manuell
2024-10-23 Grafana bei DrehschalterManuell Werte ausblenden
2024-10-25 temp 9
2024-10-25 Dokumentation
2024-10-27 Dokumentation, cleanup
2024-10-27 Dokumentation Korrekturen
2024-11-01 Dokumentation Schwaden
2024-11-01 Dokumentation google suche
2024-11-01 Legionellen kill vereinfacht
2024-11-01 Bugfix: brenner.cancel_error()
2024-11-01 statische codeanalyse
2024-11-02 Burnout laenger
2024-11-02 Cleanup
2024-11-02 Dokumentation Links
2024-11-02 Influxdb: Oekofen Brenner Start
2024-11-06 Test simplify valve count
2024-11-08 Versuch ENABLE_TFV_ADAPTIV
2024-11-08 Bugfix legionellen-kill screw up
2024-11-08 test_modulation_soll() aktualisieren
2024-11-08 ABSCHALTGRENZE_INDIVIDUELL
2024-11-08 neustart pico dezentral: hausreihe nicht sofort wärmen
2024-11-09 TPV_TEMPERATURHUB_C
2024-11-09 Neu: burnout für jeden Brenner
2024-11-09 Bugfix: iteration fluss
2024-11-10 sort_by_ladung_individuell_und_hausreihe_korrektur
2024-11-10 ScenarioControllerPlusEinHaus
2024-11-12 abschaltgrenze_band
2024-11-13 zweiter Brenner zünden Sperrzeit hoeher
2024-11-15 Optimierungen zweiter Brenner
2024-11-15 mbus-influxdb
2024-11-15 sp_verbrauch_median_W
2024-11-16 modulo_24h_s korrigiert
2024-11-17 Vorausschauend laden
2024-11-17 sp_dezentral_vorausschauend_laden optimiert
2024-11-22 Winter optimiert
2024-11-23 temp Vorladen
2024-11-24 Vorladen optimiert
2024-11-25 Korrektur Vorladen
2024-11-25 Vorladung temp01
2024-11-26 Vorladung temp02
2024-11-26 Vorladen temp03
2024-11-26 Doku Schemas
2024-11-26 Vorlagen temp03
2024-11-27 haeuser_ladung_avg_soll_prozent angepasst
2024-12-01 Vorladen optimiert, modulation 30 min action time
2024-12-01 Vorladen optimiert, fehler weg
2024-12-04 Voladen: modulation reduzieren eingebaut
2024-12-04 Vorzeichen
2024-12-05 Vorladen offset
2024-12-06 Leistung Brenner angepasst
2024-12-09 Zweiter brenner optimiert
2024-12-12 Tvf anheben mit Ladzung Zentral über 70
2024-12-17 Leistung Brenner gemessen
2024-12-17 Bildgrösse
2024-12-19 Bugfix: Brenner mit Störgung, anderer Brenner übernimmt
2024-12-19 Neu: ZUENDEN_KESSEL_WARM
2024-12-25 Fix: oekofen_AMBIENT_TEMP_C below 0C
2024-12-27 Dezentral optimiert
2024-12-29 Oekofen Register
2024-12-29 Mehr Energiereserve wenn kalt
2024-12-29 Pelletsilo symmetrie
2025-01-11 Rauch
2025-02-08 offene Fragen
2025-02-08 Russ im Kamin
2025-02-08 Erfahrung Automatik
2025-02-08 Pelletsilo symmetrie korrektur
2025-04-02 New: ScenarioOekofenBrennerModulationFreeze
2025-04-06 Abgase
2025-04-30 sp_temperatur 80 -> 76
2025-04-30 haus_maerki_ladet_haus_seinet
2025-05-18 Link
2025-06-29 pico firmware: Add the patches to the micropython repo
2025-07-27 Abklaerungen
2025-09-21 Test Manuell
2025-11-14 optimierung haus 13 solar

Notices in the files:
steuerung_automatik/hardware/kicad_dezentral/filament_dryer.kicad_pcb:
Released under MIT Open-source License
parts and their libraries:
License: CC BY 4.0
